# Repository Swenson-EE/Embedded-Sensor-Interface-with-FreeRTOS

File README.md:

# Embedded Sensor Interface with FreeRTOS

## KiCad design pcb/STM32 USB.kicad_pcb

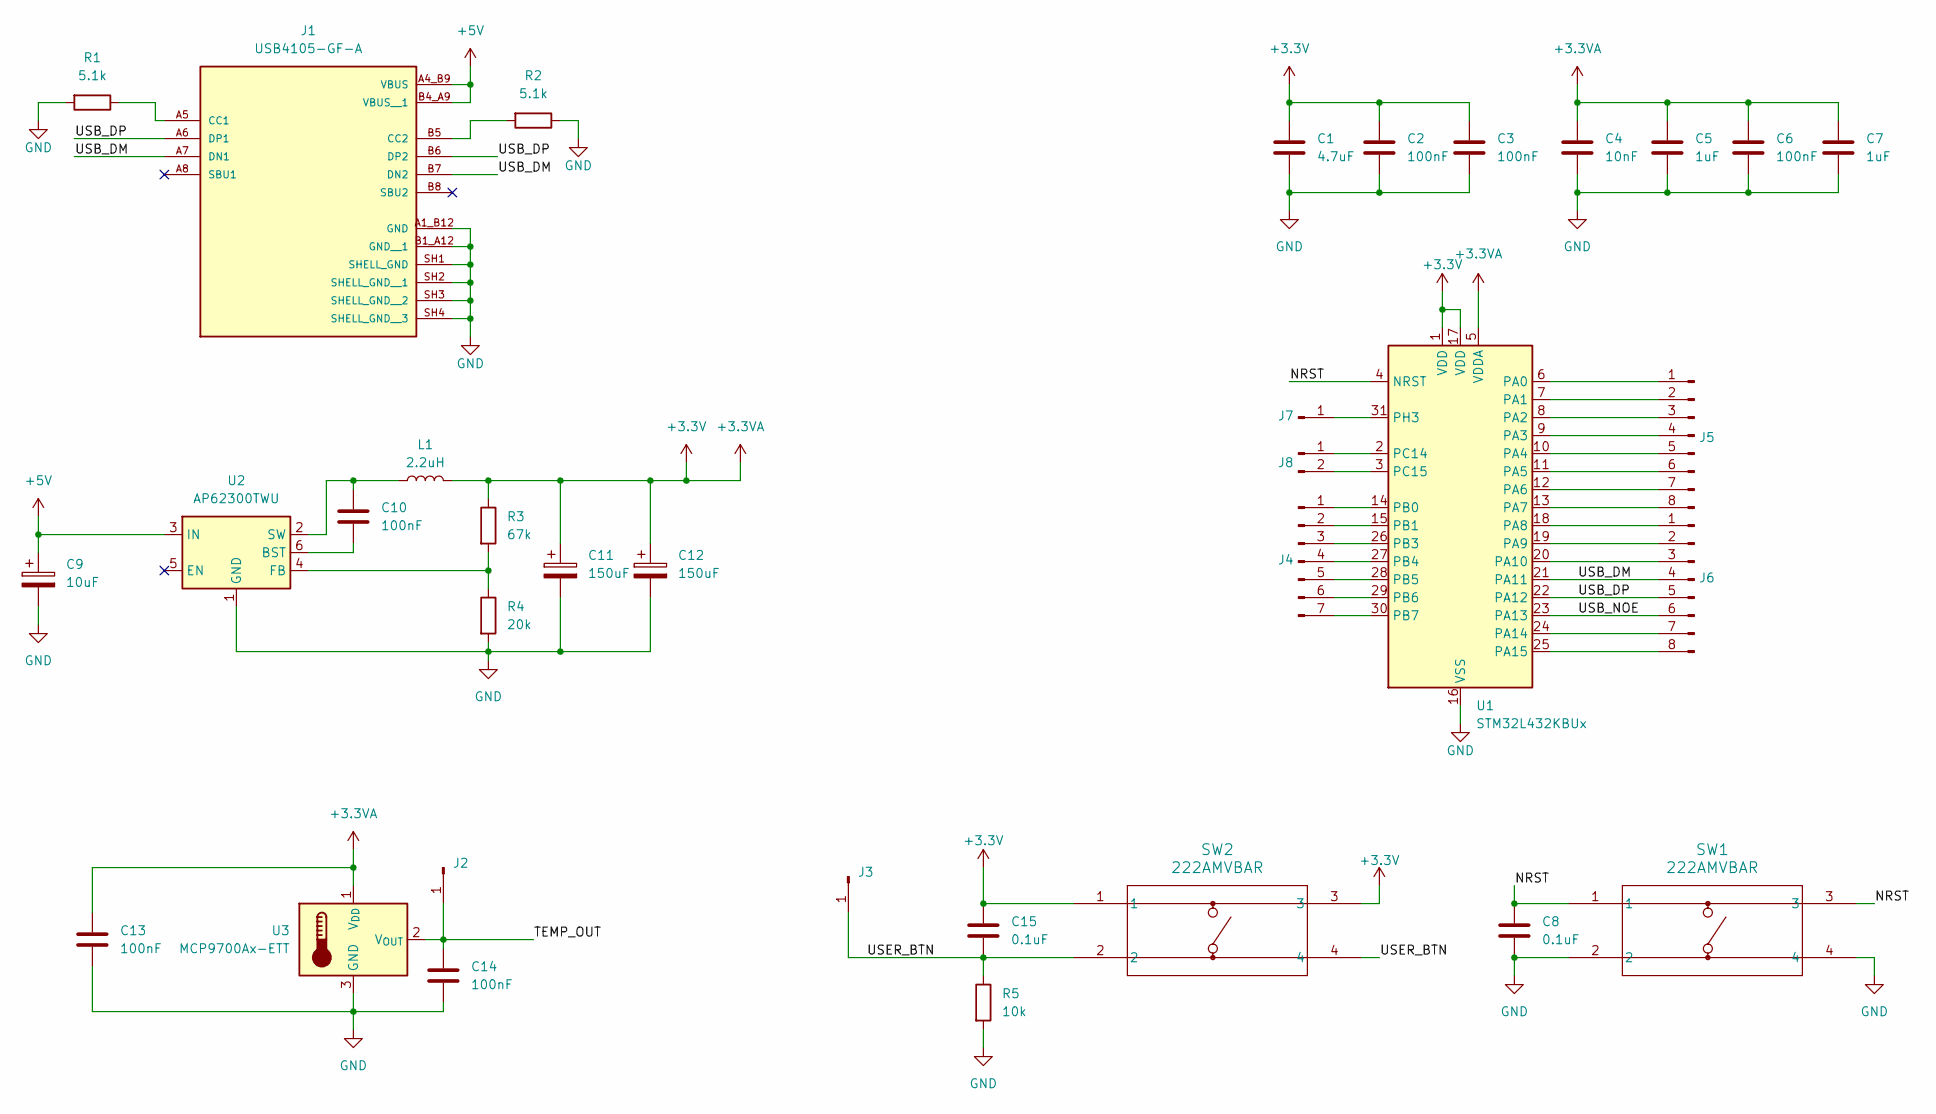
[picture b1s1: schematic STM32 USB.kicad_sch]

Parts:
C1: 4.7uF; C_0201_0603Metric
C2, C3, C6, C10, C13, C14: 100nF; C_0201_0603Metric
C4: 10nF; C_0201_0603Metric
C5, C7: 1uF; C_0201_0603Metric
C8, C15: 0.1uF; C_0201_0603Metric
C9: 10uF; CP_Elec_5x5.3
C11, C12: 150uF; CP_Elec_10x10
J1: USB4105-GF-A; GCT_USB4105-GF-A; PARTREV B4
J2, J3, J7: Conn_01x01_Pin; PinHeader_1x01_P2.54mm_Vertical
J4: Conn_01x07_Pin; PinHeader_1x07_P2.54mm_Vertical
J5, J6: Conn_01x08_Pin; PinHeader_1x08_P2.54mm_Vertical
J8: Conn_01x02_Pin; PinHeader_1x02_P2.54mm_Vertical
L1: 2.2uH; L_0603_1608Metric_Pad1.05x0.95mm_HandSolder
R1, R2: 5.1k; R_0603_1608Metric_Pad0.98x0.95mm_HandSolder
R3: 67k; R_0603_1608Metric_Pad0.98x0.95mm_HandSolder
R4: 20k; R_0603_1608Metric_Pad0.98x0.95mm_HandSolder
R5: 10k; R_0603_1608Metric_Pad0.98x0.95mm_HandSolder
SW1, SW2: 222AMVBAR
U1: STM32L432KBUx; QFN-32-1EP_5x5mm_P0.5mm_EP3.45x3.45mm
U2: AP62300TWU; TSOT-23-6
U3: MCP9700Ax-ETT; SOT-23

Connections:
+3.3V: C1.1, C2.1, C3.1, C4.1, C5.1, C6.1, C7.1, C11.1, C12.1, C13.1, C15.1, L1.2, R3.1, SW2.1, SW2.3, U1.1 (VDD), U1.5 (VDDA), U1.17 (VDD), U3.1 (V_{DD})
+5V: C9.1, J1.A4_B9 (VBUS), J1.B4_A9 (VBUS__1), U2.3 (IN)
/NRST: C8.1, SW1.1, SW1.3, U1.4 (NRST)
/TEMP_OUT: C14.1, J2.1, U3.2 (V_{OUT})
/USB_DM: J1.A7 (DN1), J1.B7 (DN2), J6.4, U1.21 (PA11)
/USB_DP: J1.A6 (DP1), J1.B6 (DP2), J6.5, U1.22 (PA12)
/USB_NOE: J6.6, U1.23 (PA13)
/USER_BTN: C15.2, J3.1, R5.1, SW2.2, SW2.4
GND: C1.2, C2.2, C3.2, C4.2, C5.2, C6.2, C7.2, C8.2, C9.2, C11.2, C12.2, C13.2, C14.2, J1.A1_B12 (GND), J1.B1_A12 (GND__1), J1.SH1 (SHELL_GND), J1.SH2 (SHELL_GND__1), J1.SH3 (SHELL_GND__2), J1.SH4 (SHELL_GND__3), R1.2, R2.1, R4.2, R5.2, SW1.2, SW1.4, U1.16 (VSS), U1.32 (VSS), U1.33 (VSS), U2.1 (GND), U3.3 (GND)
unnamed: J1.A5 (CC1), R1.1
unnamed: J1.B5 (CC2), R2.2
unnamed: J4.1, U1.14 (PB0)
unnamed: J4.2, U1.15 (PB1)
unnamed: J4.3, U1.26 (PB3)
unnamed: J4.4, U1.27 (PB4)
unnamed: J4.5, U1.28 (PB5)
unnamed: J4.6, U1.29 (PB6)
unnamed: J4.7, U1.30 (PB7)
unnamed: J5.1, U1.6 (PA0)
unnamed: J5.2, U1.7 (PA1)
unnamed: J5.3, U1.8 (PA2)
unnamed: J5.4, U1.9 (PA3)
unnamed: J5.5, U1.10 (PA4)
unnamed: J5.6, U1.11 (PA5)
unnamed: J5.7, U1.12 (PA6)
unnamed: J5.8, U1.13 (PA7)
unnamed: J6.1, U1.18 (PA8)
unnamed: J6.2, U1.19 (PA9)
unnamed: J6.3, U1.20 (PA10)
unnamed: J6.7, U1.24 (PA14)
unnamed: J6.8, U1.25 (PA15)
unnamed: J7.1, U1.31 (PH3)
unnamed: J8.1, U1.2 (PC14)
unnamed: J8.2, U1.3 (PC15)
unnamed: C10.2, U2.6 (BST)
unnamed: R3.2, R4.1, U2.4 (FB)
unnamed: C10.1, L1.1, U2.2 (SW)

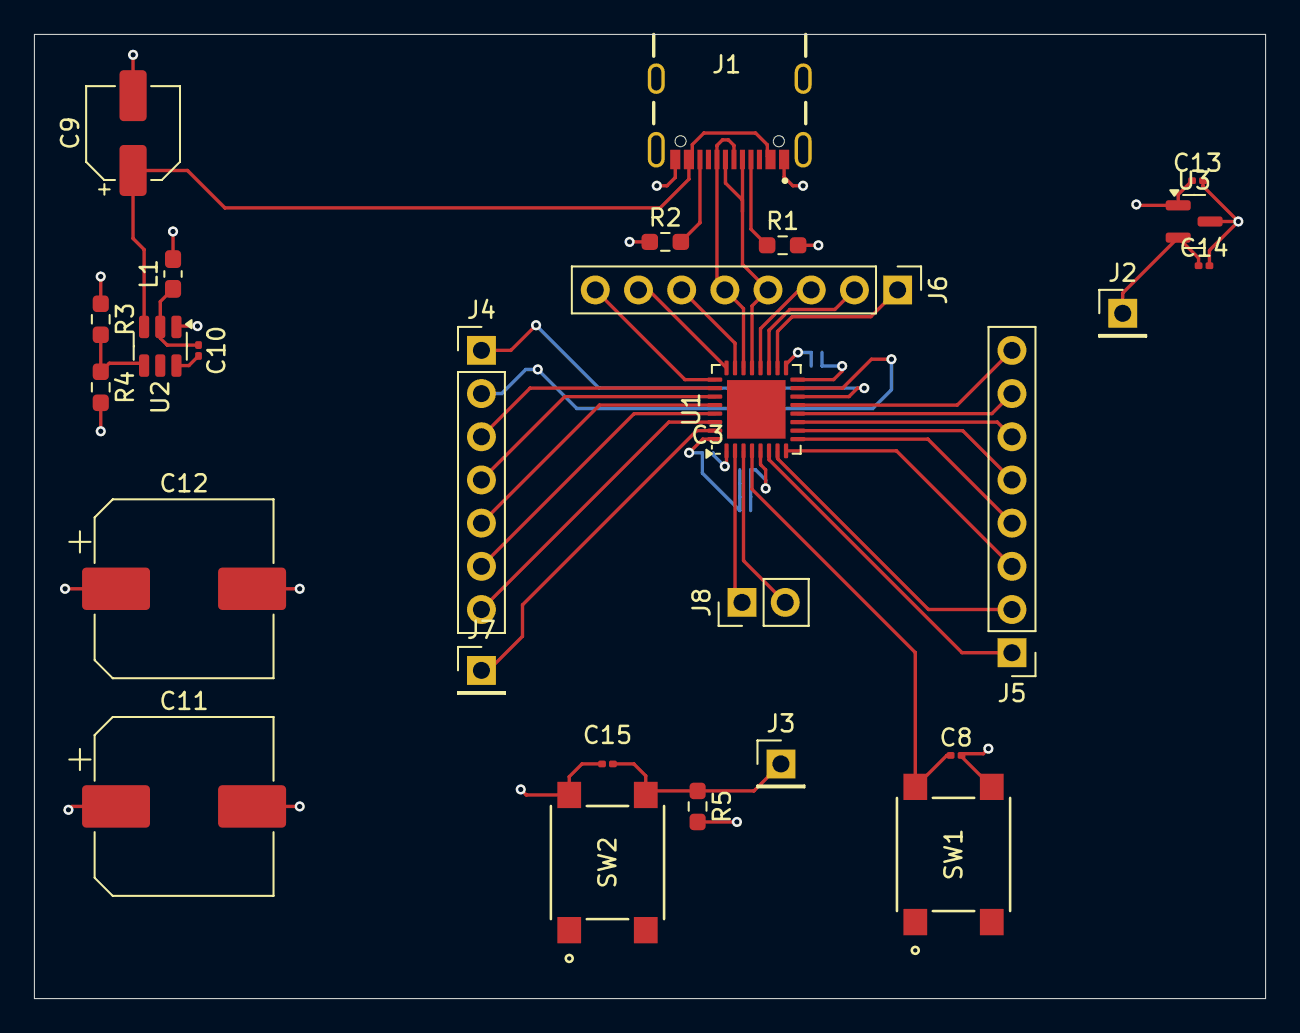
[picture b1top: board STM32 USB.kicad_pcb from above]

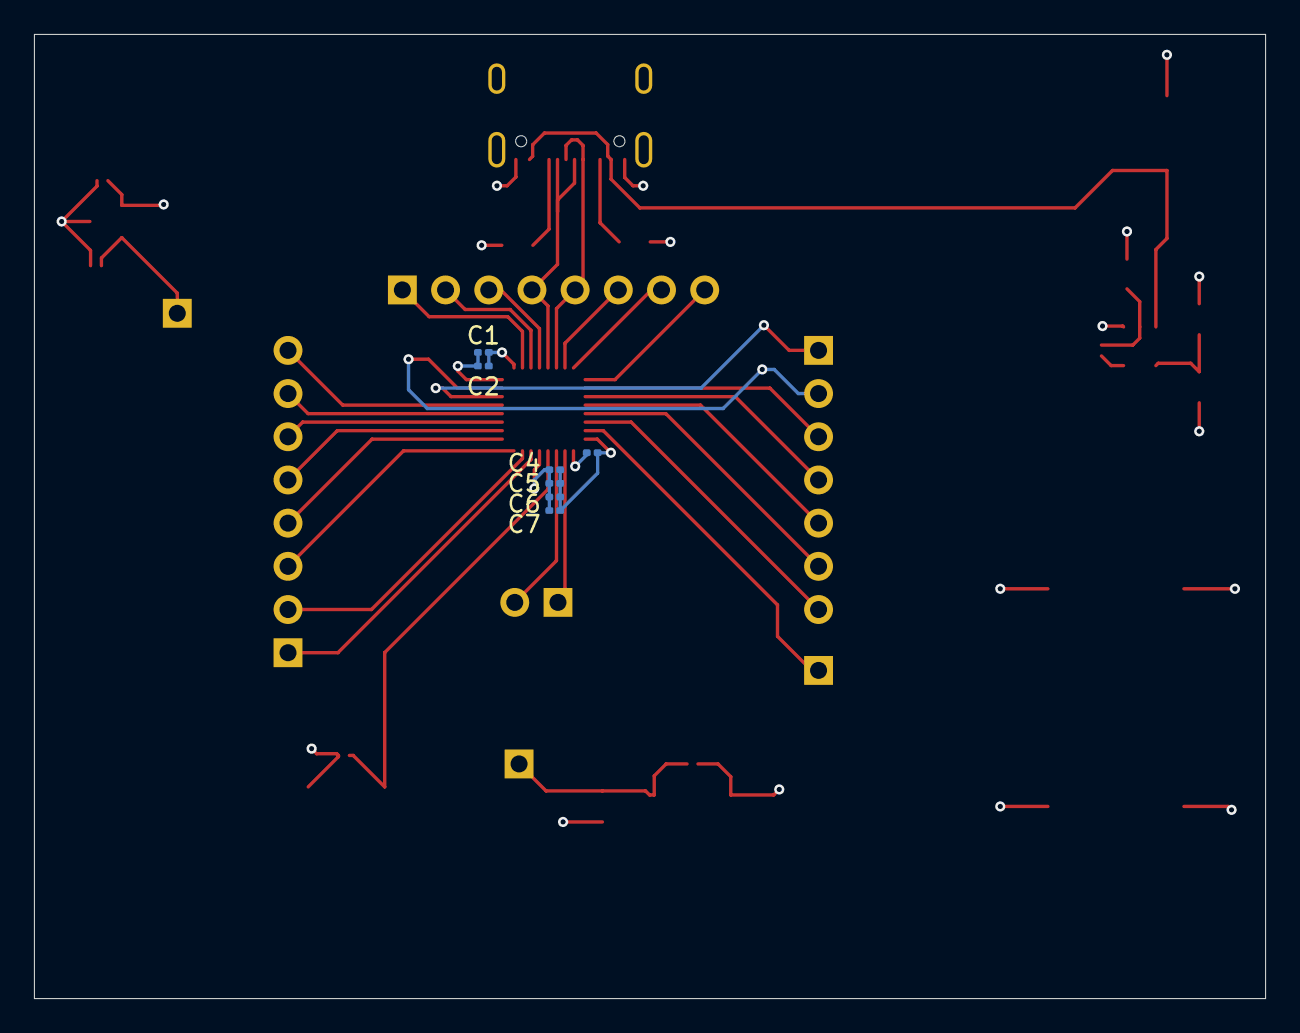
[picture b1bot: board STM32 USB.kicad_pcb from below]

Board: 4 copper layers, 72.4 x 56.7 mm, 34 parts (7 on the bottom side), 37 nets.

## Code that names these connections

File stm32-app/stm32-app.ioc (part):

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Mcu.Name=STM32L432K(B-C)Ux
Mcu.Package=UFQFPN32
Mcu.UserName=STM32L432KCUx
PA11.Mode=Device
PA11.Signal=USB_DM
PA12.Mode=Device
PA12.Signal=USB_DP
PA13\ (JTMS-SWDIO).Mode=Activate_NOE
PA13\ (JTMS-SWDIO).Signal=USB_NOE
RCC.HSE_VALUE=8000000
RCC.SYSCLKFreq_VALUE=16000000
RCC.SYSCLKSource=RCC_SYSCLKSOURCE_HSI
board=custom

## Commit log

2025-06-04 Created STM32 project. Setup Clock tree and USB peripheral
2025-06-04 Added STM32L432KC datasheet.
2025-06-17 Added Tinyusb driver and config
2025-06-17 Added base BOM and .gitignore for microsoft files
2025-06-17 Fixed BOM formatting
2025-06-17 MCU Materials
2025-06-17 Added Temperature Sensor
2025-06-17 Added USB NOE
2025-06-17 KiCAD gitignore
2025-06-17 MCU with filtering capacitors schematic
2025-06-17 Added pushbutton for mcu reset
2025-06-17 Pushbutton for reset
2025-06-17 Added ignore for #auto_saved_files#
2025-06-17 Added USB C receptacle components
2025-06-17 Added USB C components to schematic
2025-06-17 Voltage regulator components
2025-06-17 Voltage regulator calculations
2025-06-17 Voltage regulator schematic
2025-06-17 Added components for a user pushbutton
2025-06-17 Added user pushbutton
2025-06-17 Added pin connectors
2025-06-17 Routed PCB
2025-06-22 Added MCP970X datasheet
